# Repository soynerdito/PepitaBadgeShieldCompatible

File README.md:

# PepitaBadgeShieldCompatible
BSides Badge (codename Pepita). Arduino shield compatible.

To program board use an external USBAS at 5V. Connect 5V input voltage via the pin that says 3.3V to send 5V straight to the  atmega chip. If input voltage goes to the input pin it will go through the 3.3V regulator and in my first test it didn't allowed me to program the chip.

#Configure Arduino IDE 1.6.4
Step 1:
File->Preferences
 Paste in "Additional Boards Manager URLS:" https://github.com/soynerdito/PepitaBadgeShieldCompatible/raw/master/Arduino/IDE_Board_Manager/package_bsidespr_index.json
Click OK

Step 2:
Tools->Boards->Boards Manager
	Select BSides Badge from list and click Install

Step 3: Activate the board
Tools->Boads
	Select BSides Badge 2015 from the available boards
	
Step 4: Set the programmer
Tools->Programmer
	Select USBasp

# Flashing firmware
avrdude -c usbasp -b 19200 -p atmega328p -P /dev/ttyACM0 -U flash:w:mega32p_16mhz_program_on_reset.hex

#Fuses
avrdude -c usbasp -p atmega328p -b19200 -P /dev/ttyACM0 -U lfuse:w:0xf7:m -U hfuse:w:0xdA:m -U efuse:w:0x03:m

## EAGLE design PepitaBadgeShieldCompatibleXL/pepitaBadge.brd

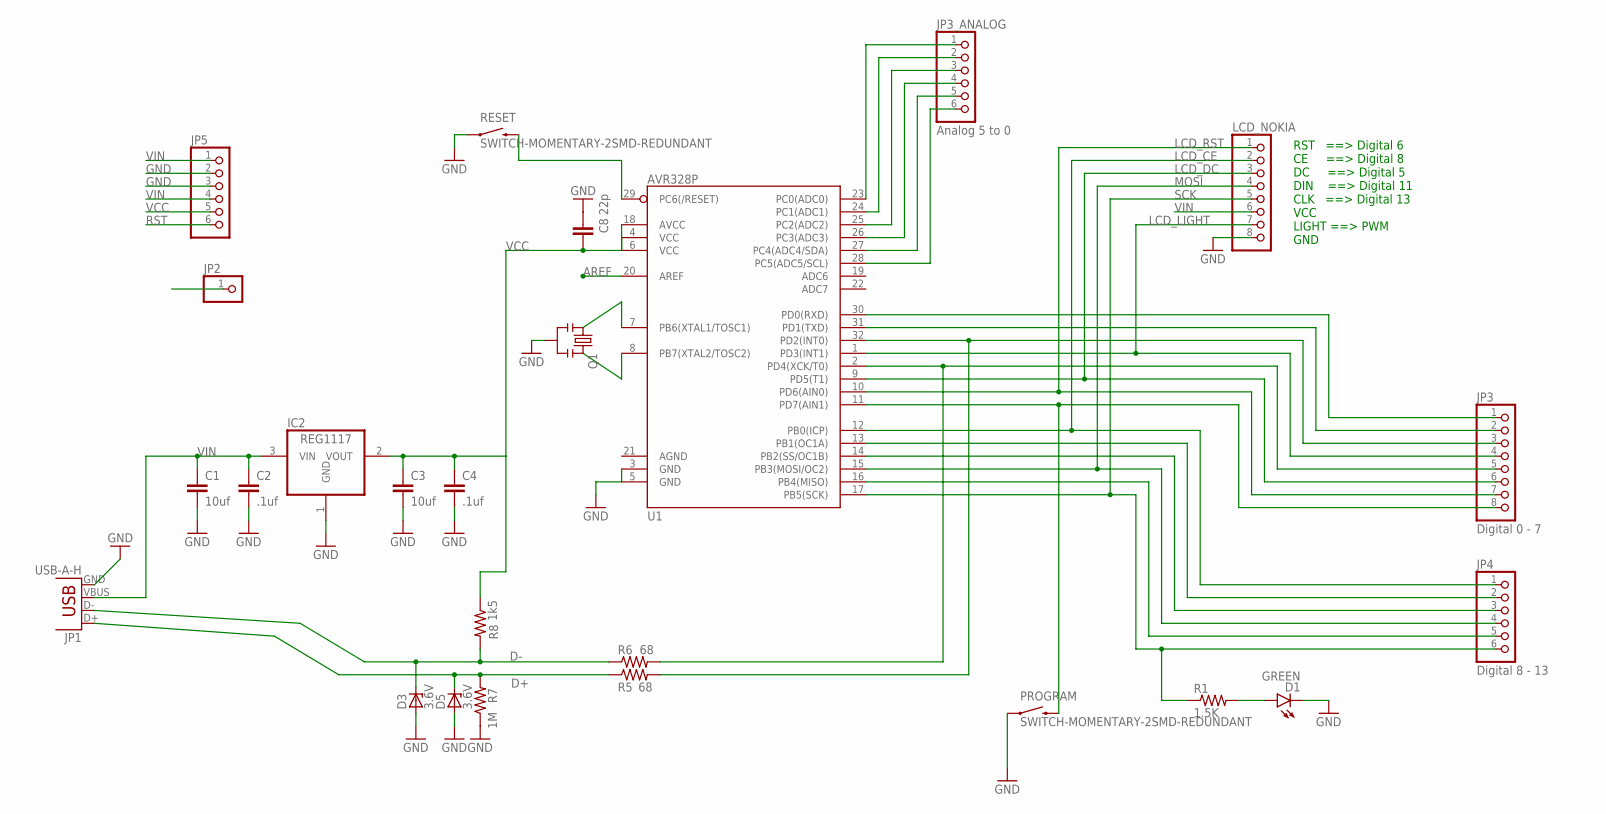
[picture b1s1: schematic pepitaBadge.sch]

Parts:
C1, C3: 10uf; 0805
C2, C4: .1uf; 0603-CAP
C8: 22p; 0603-CAP
D1: GREEN; LED-0603
D3, D5: 3.6V; 1206
IC2: REG1117; SOT223
JP1: USB-A-H
JP2: PINHD-1X1; 1X01
JP3: Digital 0 - 7; 1X08
JP3_ANALOG: Analog 5 to 0; 1X06
JP4: Digital 8 - 13; 1X06
JP5: PINHD-1X6; 1X06
LCD_NOKIA: PINHD-1X8; 1X08
PROGRAM: SWITCH-MOMENTARY-2SMD-REDUNDANT; TACTILE-SWITCH-SMD
Q1: RESONATOR16MHZ; RESONATOR-SMD
R1: 1.5K; 0603-RES
R5, R6: 68; 0603-RES
R7: 1M; 0603-RES
R8: 1k5; 0603-RES
RESET: SWITCH-MOMENTARY-2SMD-REDUNDANT; TACTILE-SWITCH-SMD
U1: AVR328P; TQFP32-08

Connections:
A5: JP3_ANALOG.6, U1.28 (PC5(ADC5/SCL))
AREF: JP2.1, U1.20 (AREF)
D+: D5.2 (C), JP1.D+, R5.1, R7.2
D-: D3.2 (C), JP1.D-, R6.1, R8.2
GND: C1.2, C2.2, C3.2, C4.2, C8.2, D1.C, D3.1 (A), D5.1 (A), IC2.1 (GND), JP1.GND, JP5.2, JP5.3, LCD_NOKIA.8, PROGRAM.1, PROGRAM.2 (1), Q1.2, R7.1, RESET.1, RESET.2 (1), U1.3 (GND), U1.5 (GND)
LCD_CE: JP4.1, LCD_NOKIA.2, U1.12 (PB0(ICP))
LCD_DC: JP3.6, LCD_NOKIA.3, U1.9 (PD5(T1))
LCD_LIGHT: JP3.4, LCD_NOKIA.7, U1.1 (PD3(INT1))
LCD_RST: JP3.7, LCD_NOKIA.1, U1.10 (PD6(AIN0))
MISO: JP4.5, U1.16 (PB4(MISO))
MOSI: JP4.4, LCD_NOKIA.4, U1.15 (PB3(MOSI/OC2))
unnamed: D1.A, R1.2
unnamed: JP3_ANALOG.5, U1.27 (PC4(ADC4/SDA))
unnamed: JP3_ANALOG.4, U1.26 (PC3(ADC3))
unnamed: JP3_ANALOG.3, U1.25 (PC2(ADC2))
unnamed: JP3.5, R6.2, U1.2 (PD4(XCK/T0))
unnamed: JP3_ANALOG.2, U1.24 (PC1(ADC1))
unnamed: Q1.1, U1.7 (PB6(XTAL1/TOSC1))
unnamed: JP3_ANALOG.1, U1.23 (PC0(ADC0))
unnamed: Q1.3, U1.8 (PB7(XTAL2/TOSC2))
unnamed: JP4.2, U1.13 (PB1(OC1A))
unnamed: JP4.3, U1.14 (PB2(SS/OC1B))
unnamed: JP3.3, R5.2, U1.32 (PD2(INT0))
PD7: JP3.8, PROGRAM.3 (2), PROGRAM.4 (2), U1.11 (PD7(AIN1))
RST: JP5.6, RESET.3 (2), RESET.4 (2), U1.29 (PC6(/RESET))
RXD: JP3.1, U1.30 (PD0(RXD))
SCK: JP4.6, LCD_NOKIA.5, R1.1, U1.17 (PB5(SCK))
TXD: JP3.2, U1.31 (PD1(TXD))
VCC: C3.1, C4.1, C8.1, IC2.2 (VOUT), JP5.5, R8.1, U1.4 (VCC), U1.6 (VCC), U1.18 (AVCC)
VIN: C1.1, C2.1, IC2.3 (VIN), JP1.VBUS, JP5.1, JP5.4, LCD_NOKIA.6

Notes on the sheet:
RST ==> Digital 6 CE ==> Digital 8 DC ==> Digital 5 DIN ==> Digital 11 CLK ==> Digital 13 VCC LIGHT ==> PWM GND

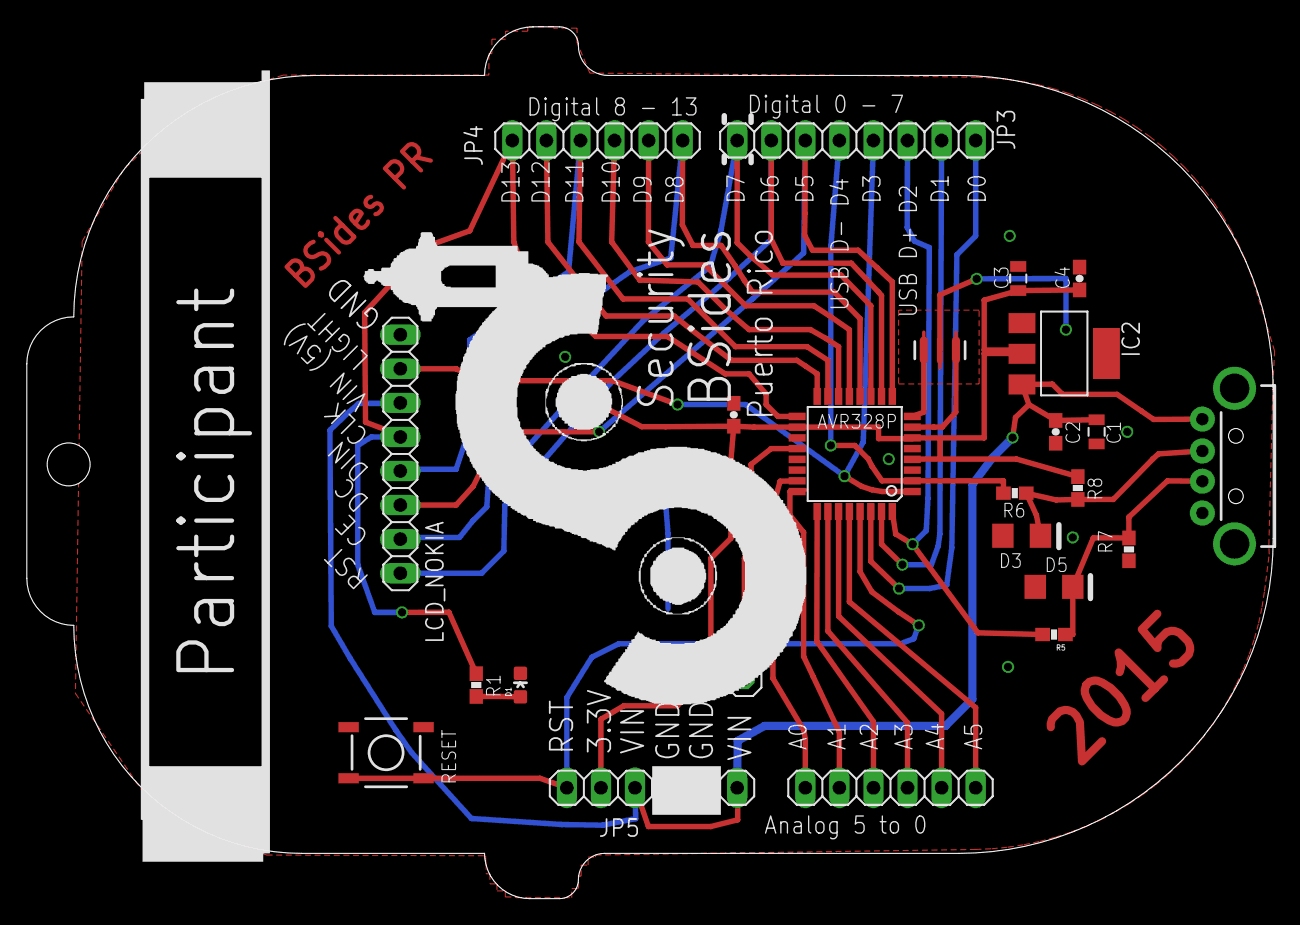
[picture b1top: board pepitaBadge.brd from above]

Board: 2 copper layers, 92.9 x 65.0 mm, 27 parts (1 on the bottom side), 30 nets.

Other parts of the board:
U$2: OBSIDISLOGO_BOTTOM
U$5: BSIDES_LOGO_NTB_PIC_ONLY

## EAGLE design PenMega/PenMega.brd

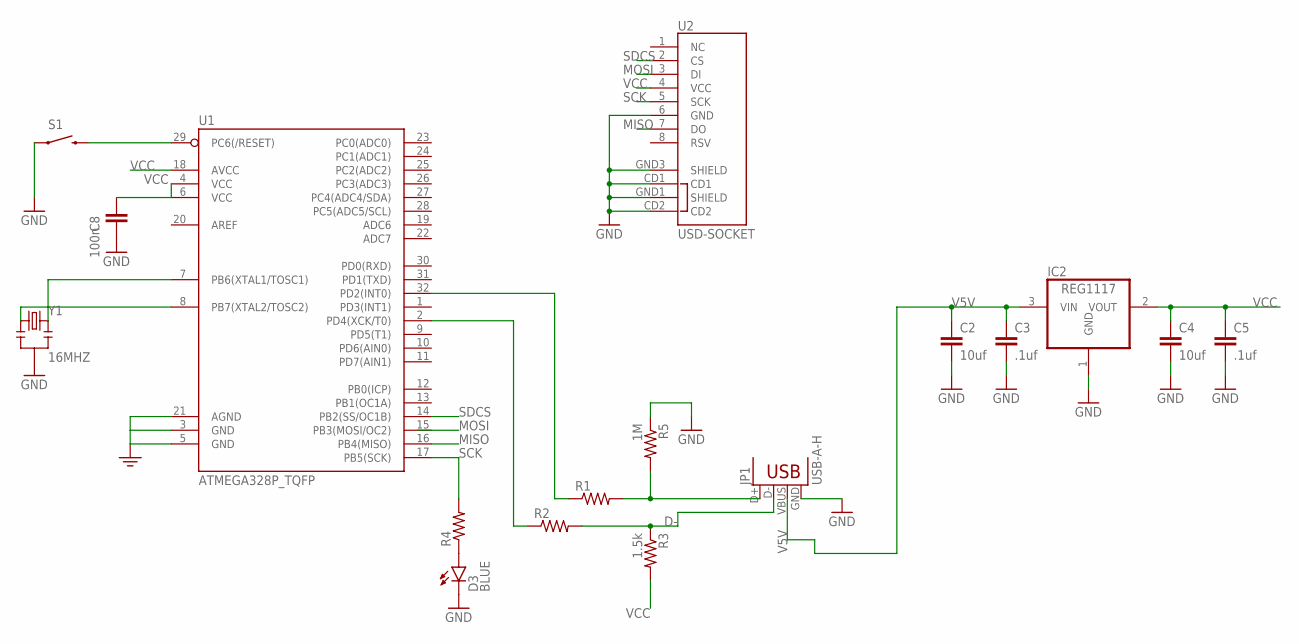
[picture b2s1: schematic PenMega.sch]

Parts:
C2, C4: 10uf; 0805
C3, C5: .1uf; 0603-CAP
C8: 100n; 0603-CAP
D3: BLUE; LED-0603
IC2: REG1117; SOT223
JP1: USB-A-H
R1, R2, R4: RESISTOR0603-RES; 0603-RES
R3: 1.5k; 0603-RES
R5: 1M; 0603-RES
S1: SWITCH-MOMENTARY-2SMD; TACTILE-SWITCH-SMD
U1: ATMEGA328P_TQFP; TQFP32-08
U2: USD-SOCKET; MICROSD_1:1
Y1: 16MHZ; RESONATOR-SMD

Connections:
D-: JP1.D-, R2.2, R3.1
GND: C2.2, C3.2, C4.2, C5.2, C8.2, D3.C, IC2.1 (GND), JP1.GND, R5.1, S1.1, U1.3 (GND), U1.5 (GND), U1.21 (AGND), U2.6 (GND), U2.CD1, U2.CD2, U2.GND1 (SHIELD), U2.GND3 (SHIELD), Y1.2
MISO: U1.16 (PB4(MISO)), U2.7 (DO)
MOSI: U2.3 (DI)
unnamed: U1.8 (PB7(XTAL2/TOSC2)), Y1.1
unnamed: U1.7 (PB6(XTAL1/TOSC1)), Y1.3
unnamed: JP1.D+, R1.2, R5.2
unnamed: R2.1, U1.2 (PD4(XCK/T0))
unnamed: R1.1, U1.32 (PD2(INT0))
unnamed: S1.3 (2), U1.29 (PC6(/RESET))
unnamed: D3.A, R4.1
SCK: R4.2, U1.17 (PB5(SCK)), U2.5 (SCK)
SDCS: U1.14 (PB2(SS/OC1B)), U2.2 (CS)
V5V: C2.1, C3.1, IC2.3 (VIN), JP1.VBUS
VCC: C4.1, C5.1, C8.1, IC2.2 (VOUT), R3.2, U1.4 (VCC), U1.6 (VCC), U1.18 (AVCC), U2.4 (VCC)

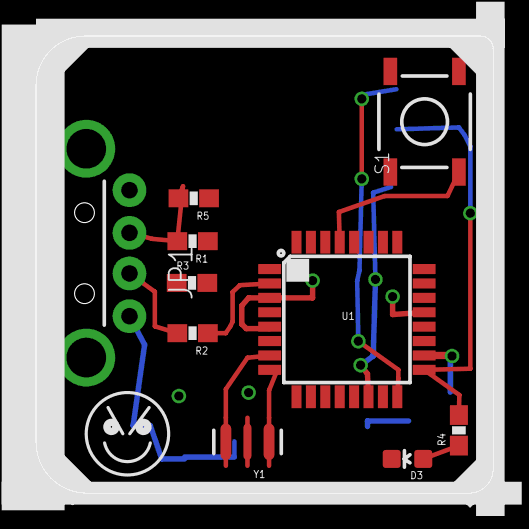
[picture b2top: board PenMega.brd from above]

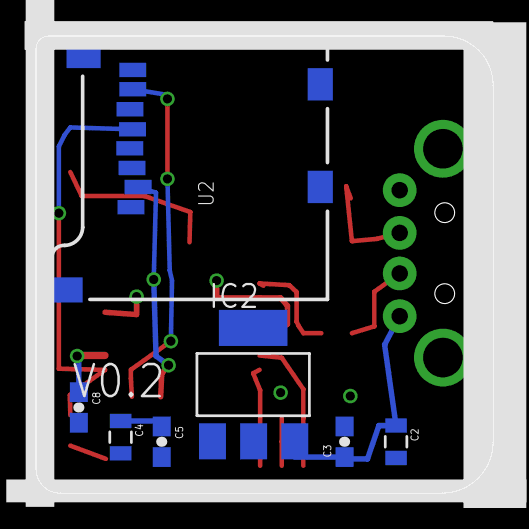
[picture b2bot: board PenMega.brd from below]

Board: 2 copper layers, 25.4 x 25.4 mm, 17 parts (7 on the bottom side), 14 nets.

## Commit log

2015-04-09 Update gitignore
2015-04-09 Adding Eagle Files
2015-04-11 Adding firmware files
2015-04-11 Creating readme
2015-04-11 Small fixes to XL design
2015-04-11 Adding some pictures
2015-04-11 Adding instruction on how to flash using Arduino as an ISP
2015-04-12 Smooth PCB border and adding some Arduino code
2015-04-20 Trying to make this work, as of now first sent to manufacturing did not work with 6mills paths. changed to 10 mills.
2015-04-21 Partial fix for penmega. Removed un needed zener diodes
2015-04-24 Partially working on fixing PenMega. Work in progress
2015-05-02 Actual Gebers to be ordered for Staff and Speakers
2015-05-06 Participant gerbers
2015-05-07 Participant gerbers fix
2015-05-24 Scritps used for automating fimrware flash
2015-05-28 Some images
2015-05-28 Fix size and fixed readme
2015-05-28 Adding files to import on Arduino 1.6.4
2015-05-28 Syntax error
2015-05-28 Syntax fix
2015-05-28 fix boards.txt
2015-05-28 Version increment
2015-05-28 How to Configure Arduino 1.6.4
2015-05-28 reducing size
2015-05-29 fixing
2015-05-29 continue my ...
2015-05-29 How to configure Badge on Arduino IDE
2015-05-29 Adding Keyboard Library
2015-05-29 fixing file bz2 format
2015-05-30 Update README.md
    Set the programmer to usbasp.
2016-12-04 Try for upgrade of arduino compatibility

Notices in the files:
parts and their libraries:
SparkFun-DigitalIC: Licensing: Creative Commons ShareAlike 4.0 International - https://creativecommons.org/licenses/by-sa/4.0
